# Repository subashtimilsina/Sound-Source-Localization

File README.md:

# Sound source localization

This project estimates **where a sound is coming from** in **3D** using a **cubical eight-microphone array**. It combines **GCC-PHAT** with a **grid search** over azimuth and elevation. Audio is processed at **16 kHz** on a **Raspberry Pi**; estimated angles are sent over **serial** to a **microcontroller**, which handles low-level **motion and control** of the robot.

If you **do not** wish to build the robot and only need the **software and testing**, see **[Running the main SSL pipeline](#running-the-main-ssl-pipeline)** (use the desktop scripts for bench runs without the physical robot).

<p align="center">
  <a href="https://github.com/subash-timilsina/Sound-Source-Localization-Hardware"><b>Hardware and Firmware (build the robot)</b></a>
  &nbsp;·&nbsp;
  <a href="http://idl.iscram.org/files/abhishkhanal/2020/2293_AbhishKhanal_etal2020.pdf"><b>ISCRAM 2020 paper (PDF)</b></a>
</p>

The **mechanical parts, electronics, and firmware** for the physical robot live in a separate hardware repository. This repository is focused on **software**: real-time localization scripts plus **optional** notebooks and experiments you can use for **testing, calibration, and research** without changing the main pipeline.

---

## What you are building, end to end

Think of the system in three layers: **sensors**, **compute**, and **actuation**.

1. **Robot and array (hardware repository)**  
   You assemble the mobile platform, power, motor drivers, microcontroller, and the **cubic microphone frame** so that eight microphone channels reach the computer that will run Python.

2. **Sound localization (this repository, on the Raspberry Pi)**  
   The Pi captures **eight channels** (today’s scripts assume two **four-input** audio devices, or equivalent routing). It runs **GCC-PHAT** and a **spherical grid search** to produce **azimuth** and **elevation** estimates for the dominant source.

3. **Motion (microcontroller)**  
   The Pi does **not** replace the MCU for motor timing. It sends **UART packets** with the estimated angles. Your **firmware** on the microcontroller decodes those bytes and drives the robot (wheels, servos, etc.) according to your control logic.

So: **build the robot from the hardware repo → mount the Pi and cube array → run the Pi script → the Pi streams angle updates to the MCU**, which closes the loop to the physical world.

```mermaid
flowchart LR
  A[Hardware repo:\nassemble robot and array] --> B[Cubic array +\nRaspberry Pi]
  B --> C["Pi: SSL Python script\n(GCC-PHAT + grid)"]
  C --> D[UART serial]
  D --> E[Microcontroller\nmotors / behavior]
```

---

## Figures

Pictures in [`pics/`](pics/) illustrate the **sensor head** and the **full robot** you integrate with the pipeline above.

| File | What it shows |
|------|----------------|
| [`pics/cube_array.jpg`](pics/cube_array.jpg) | The **cubical microphone array**: rigid frame, microphone boards, and wiring into the interface that feeds the Pi. |
| [`pics/Robot.jpg`](pics/Robot.jpg) | The **complete mobile platform**: Pi, batteries, motor electronics, emergency stop, and the elevated structure carrying the array. |

**Cubic microphone array** (eight channels in a fixed geometry, feeding the localization code):

**Mobile robot** (Pi + MCU + mechanics; the Pi runs SSL and talks to the MCU over serial):

---

## Running the main SSL pipeline

All **production-style** real-time runners live at the **repository root**. You edit **device indices**, and on the Pi **serial port and baud**, inside the files listed below.

| Role | Script | Notes |
|------|--------|--------|
| **Raspberry Pi + robot** (energy gate, **UART** to MCU) | `python Grid_Real_time_raspberrypi.py` | Use this after you assemble hardware: captures audio, estimates direction, **writes angles to serial**. Adjust `serial.Serial(...)` (e.g. `/dev/ttyS0`, baud `9600`) and **`device_index1` / `device_index2`** for your two four-channel interfaces. |
| **Desktop / lab** (terminal output, **WebRTC VAD**) | `python Grid_Real_time.py` | Handy for **bench testing** the same DSP path without the robot serial link. |
| **Desktop / lab** (live **3D plot**) | `python Grid_Real_time_GUI.py` | Same core idea with a **matplotlib** view of the estimated direction. |

**Finding audio devices:** set `device_index1` and `device_index2` in the script to match PyAudio (or use helper notebooks under `Initial Codes/` if you need to enumerate devices interactively).

**Microcontroller side:** the Pi script uses a **start byte** and **custom packing** in `write_data()` when it sends azimuth and elevation. Your **MCU firmware must match** that format so angles are interpreted correctly.

**Dependencies (typical):** Python 3, `numpy`, `scipy`, `pyaudio`; for desktop scripts also `webrtcvad`, and for the GUI `matplotlib`; for the Pi runner **`pyserial`**. Install `soundfile` if you use code paths that require it.

---

## Other folders (optional — testing and exploration)

These directories are **not required** to run `Grid_Real_time_raspberrypi.py` on the robot. They are **older or parallel work**: notebooks, prototypes, and datasets useful for **debugging microphones, trying other algorithms, or analyzing recordings**.

| Folder | Purpose |
|--------|--------|
| **`Initial Codes/`** | Early **GCC-PHAT** experiments: **4-mic** and **8-mic** scripts and notebooks, **VAD**, live streaming, grid search prototypes, and small utilities (e.g. listing input devices). Good for **step-by-step testing** of audio hardware and correlation behavior before trusting the full robot loop. |
| **`MUSIC SSL/`** | Experiments with the **MUSIC** direction-finding family (**notebooks** and scripts). Independent of the default GCC-PHAT grid pipeline; useful if you want to **compare methods** or teach array processing. |
| **`Denoising and VAD/`** | **Speech vs. non-speech** classifiers (**CNN / RNN** notebooks), **denoising** models (U-Net, ResNet, CED), and preprocessing notebooks. Relevant when you care about **front-end robustness** or labeling data—not wired into the default real-time SSL scripts. |
| **`Data_From_cube/`** | Notebooks working with **recorded data** from the cube-style array (e.g. analysis and tests on saved captures rather than only live input). |
| **`Data with ps3eye/`** | Capture / organization experiments involving a **PS3 Eye**; useful for **camera–audio** or data-collection workflows, separate from the core SSL runner. |
| **`pics/`** | **Figures** for documentation (see above). |
| **`LICENSE`** | License terms for this repository. |

Together, these folders support **development and validation**. The **minimal path on the real robot** remains: hardware from the companion repo, then **`Grid_Real_time_raspberrypi.py`** on the Pi with correct audio and serial settings.

---

### Citation

If you use this work, please cite the ISCRAM 2020 proceedings paper. BibTeX:

```bibtex
@inproceedings{AbhishKhanal_etal2020,
  author    = {Khanal, Abhish and Chand, Deepak and Chaudhary, Prakash and Timilsina, Subash and Panday, Sanjeeb Prasad and Shakya, Aman and others},
  title     = {Search Disaster Victims using Sound Source Localization},
  booktitle = {ISCRAM 2020 Conference Proceedings -- 17th International Conference on Information Systems for Crisis Response and Management},
  editor    = {Hughes, Amanda and McNeill, Fiona and Zobel, Christopher W.},
  pages     = {1022--1030},
  year      = {2020},
  address   = {Blacksburg, VA, USA},
  publisher = {Virginia Tech}
}
```

## Demo video

The walkthrough is on YouTube: [watch the demo](https://www.youtube.com/watch?v=Y1u37uJwSeI).

## License

See the [`LICENSE`](LICENSE) file in this repository.

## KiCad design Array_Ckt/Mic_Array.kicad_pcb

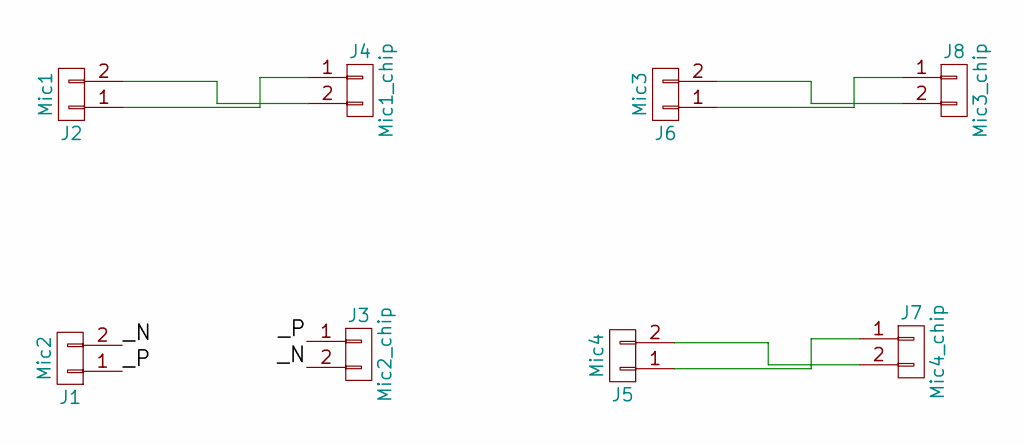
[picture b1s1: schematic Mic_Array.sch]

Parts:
J1: Mic2; Pin_Header_Straight_1x02_Pitch2.54mm
J2: Mic1; Pin_Header_Straight_1x02_Pitch2.54mm
J3: Mic2_chip; Pin_Header_Straight_1x02_Pitch2.54mm
J4: Mic1_chip; Pin_Header_Straight_1x02_Pitch2.54mm
J5: Mic4; Pin_Header_Straight_1x02_Pitch2.54mm
J6: Mic3; Pin_Header_Straight_1x02_Pitch2.54mm
J7: Mic4_chip; Pin_Header_Straight_1x02_Pitch2.54mm
J8: Mic3_chip; Pin_Header_Straight_1x02_Pitch2.54mm

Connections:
/_N: J1.2, J3.2
/_P: J1.1, J3.1
unnamed: J2.1, J4.1
unnamed: J2.2, J4.2
unnamed: J5.1, J7.1
unnamed: J5.2, J7.2
unnamed: J6.1, J8.1
unnamed: J6.2, J8.2

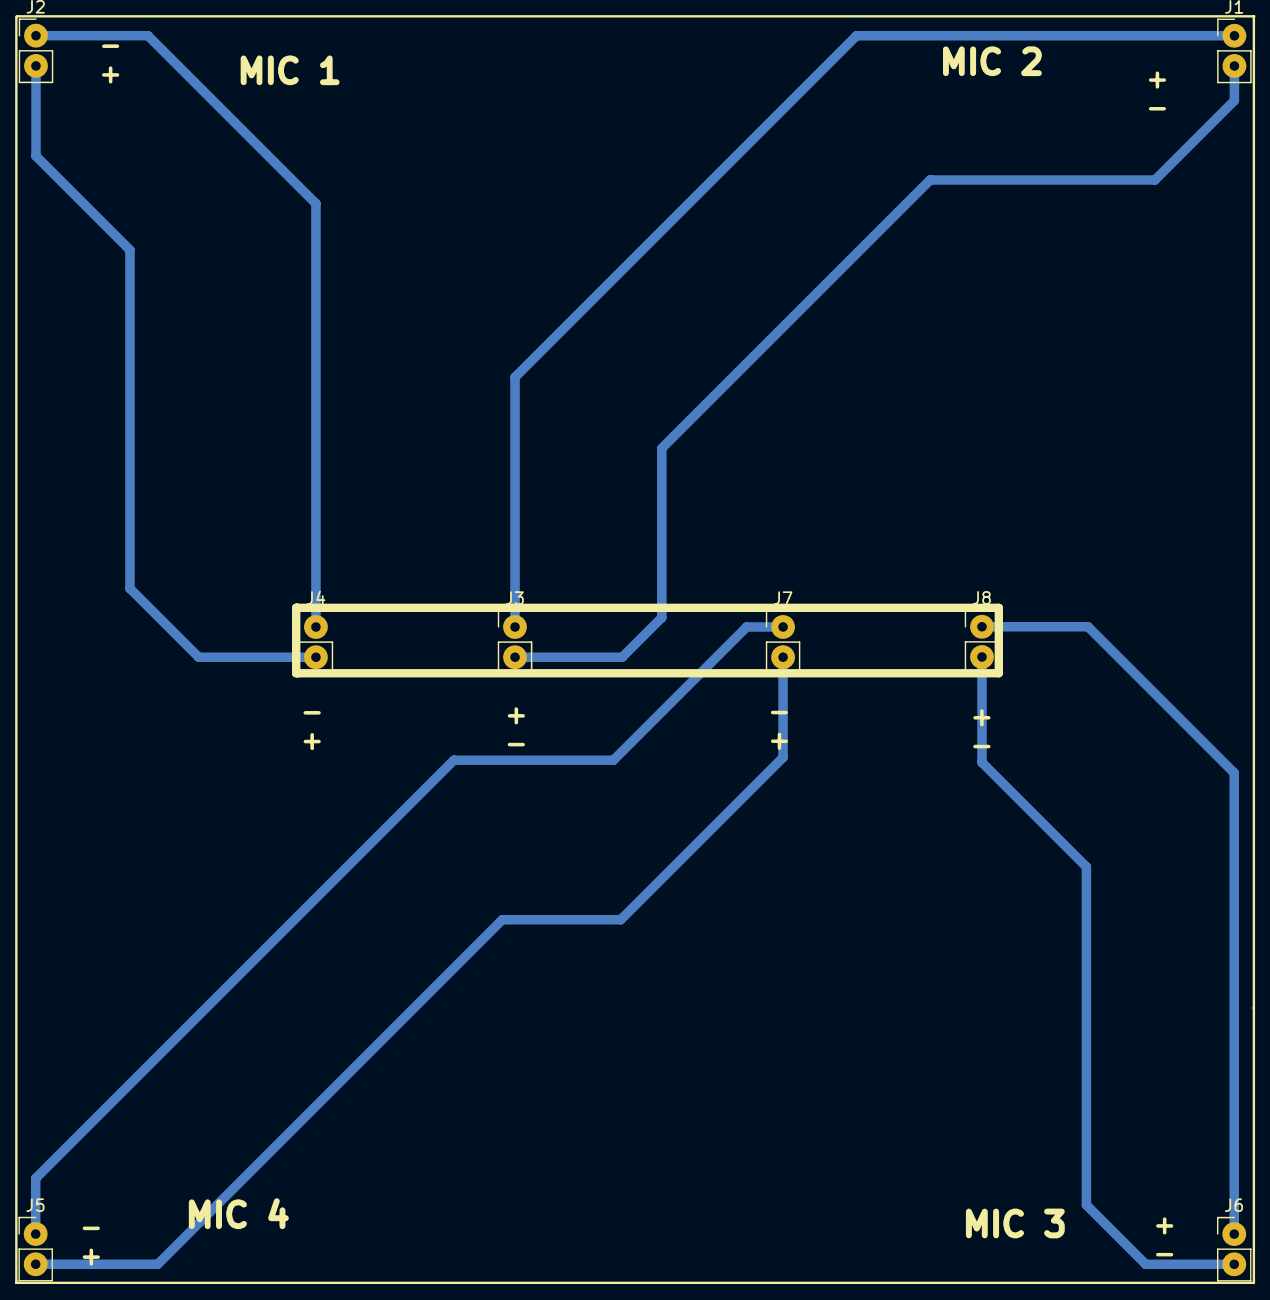
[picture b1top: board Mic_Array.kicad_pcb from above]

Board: 2 copper layers, 8 parts (0 on the bottom side), 8 nets.

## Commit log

2019-04-25 Final Year Project
2019-07-01 After cubical array
2019-07-01 old files added
2019-07-15 Grid calculation
2019-07-16 3D successfully localized
2019-07-17 Grid Optimized
2019-07-21 GUI-added
2019-07-21 Voice activity detection added
2019-07-28 Raspberry pi implementation
2019-07-28 images added
2019-07-29 managed codes
2019-07-29 gitignore folders
2019-07-29 gitignore folders added
2019-07-29 git ignored Folders
2019-07-29 Git ignore added
2019-07-29 Git ignored folder
2019-07-29 Peaks Visualized
2019-08-06 Adding AI part of the project
    Contains files for denoising and vad using different architecture.
2019-08-12 Adding U-Net model
    Not better model than FCNN
2022-04-15 Create LICENSE
2026-05-19 Documentation improved
2026-05-19 comments added
2026-05-19 Demo video link added
2026-05-19 removed extra line
2026-05-19 pipeline image added.
